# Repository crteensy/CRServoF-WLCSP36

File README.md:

# CRServoF-WLCSP36
CRSF to Servo PWM converter, using an STM32F051 in WLCSP-36

This is a different take on https://github.com/CapnBry/CRServoF, but with major differences - so no fork.

## Purpose and features
Many modern RC receivers have serial output and a number of different serial protocols. A popular one is Crossfire (or CSRF). However, in anything other than multicopters that need a flight controller, these receivers are not very useful because they don't have per-channel PWM output for servos and ESCs.

Theses RC systems also feature telemetry to get data about battery state and many other things on the ground during flight. There are a number of serial protocols for attaching sensors to a receiver for anything that the receiver can't measure itself.

Features:
- STM32F051 in WLCSP-36 *
- CRSF compatible header to attach a receiver to
- 6 Servo PWM outputs
- extra UART header for sensor communication
- Supply for external sensors, either 3V3 or 5V (solder jumper)
- VBat sensing input to an ADC channel, with an on-board divider and filter cap
- LEDs on BEC and 3V3 rails
- SWD header

It is powered by an external BEC (usually the ESC should bring one). There is no regulator on board that will handle anything above 5V. Of course it can run off a 1S LiIon, LiPo or similar battery.

\*) You might ask why I used this package. It's simple: I didn't have any other at hand, and couldn't order any similar STM32 in a more friendly package. It can still be soldered at home, though!

## Layout

The layout is simple and doesn't require special PCB fabrication technology:
- min track width / clearance: 0.1 mm
- standard vias, 0.2 mm drill / 0.5 mm outer diameter, no tenting or similar extras
- 4 layers
- single sided assembly, 0402 or larger passives

In order to route signals that do not come from pins along the perimeter, multiple pins are shorted in order to reach the perimeter. Only one of these pins may drive it at any given time.

MCU Pinout and extra pins used to route the design:

| Function | Pin (GPIO) | Extra Pins (GPIOs) | Comment
|---|---|---|---|
| NRST     | D5 | C6 (PC15) |
| BOOT0    | B4 | B5 (PF0), A6 (PC13) | 10k Pull-down
| PWM 1    | A2 (PA15) |   | TIM2_CH1, 1k series resistor (also boot loader UART Rx)
| PWM 2    | A3 (PB4) |   |  TIM3_CH1, 1k series resistor
| PWM 3    | B3 (PB3) | A4 (PB7) | TIM2_CH2, 1k series resistor
| PWM 4    | F3 (PB0) |   | TIM3_CH3, 1k series resistor
| PWM 5    | D1 (PA9) |   | TIM1_CH2, 1k series resistor
| PWM 6    | F2 (PB1) |   | TIM3_CH4, 1k series resistor
| SWCLK    | B2 (PA14) | A1 (PA12) | (also boot loader Tx, 1k series resistor)
| SWDIO    | B1 (PA13) |   |
| UART1 Tx | C4 (PB6) | C5 (PF1), B6 (PC14)  | 1k series resistor
| UART1 Rx | C1 (PA10) |   |
| UART2 Tx | E4 (PA2) | F4 (PA7) | CRSF header, 1k series resistor
| UART2 Rx | F5 (PA3) |   | CRSF header
| ADC      | F6 (PA0) |   | ADC_IN0, 10k/1k divider and filter cap
| VDD,VDDA | A5, E1, E5 | E6 (PB5) | supply
| VSS, VSSA | F1, D6 |   | GND

The boot loader UART (UART2) on PA14/PA15 can be accessed through a dedicated set of pads on the bottom. One of them (UART2_Tx) is shared with a servo output, but that doesn't hurt during programming.

If the battery voltage (to be measured with the ADC) is accidentally connected to a servo output, this will probably not cause damage because all PWM outputs have a 1k series resistor. Unless it's connected in reverse. That would be bad, even on the VBat header.

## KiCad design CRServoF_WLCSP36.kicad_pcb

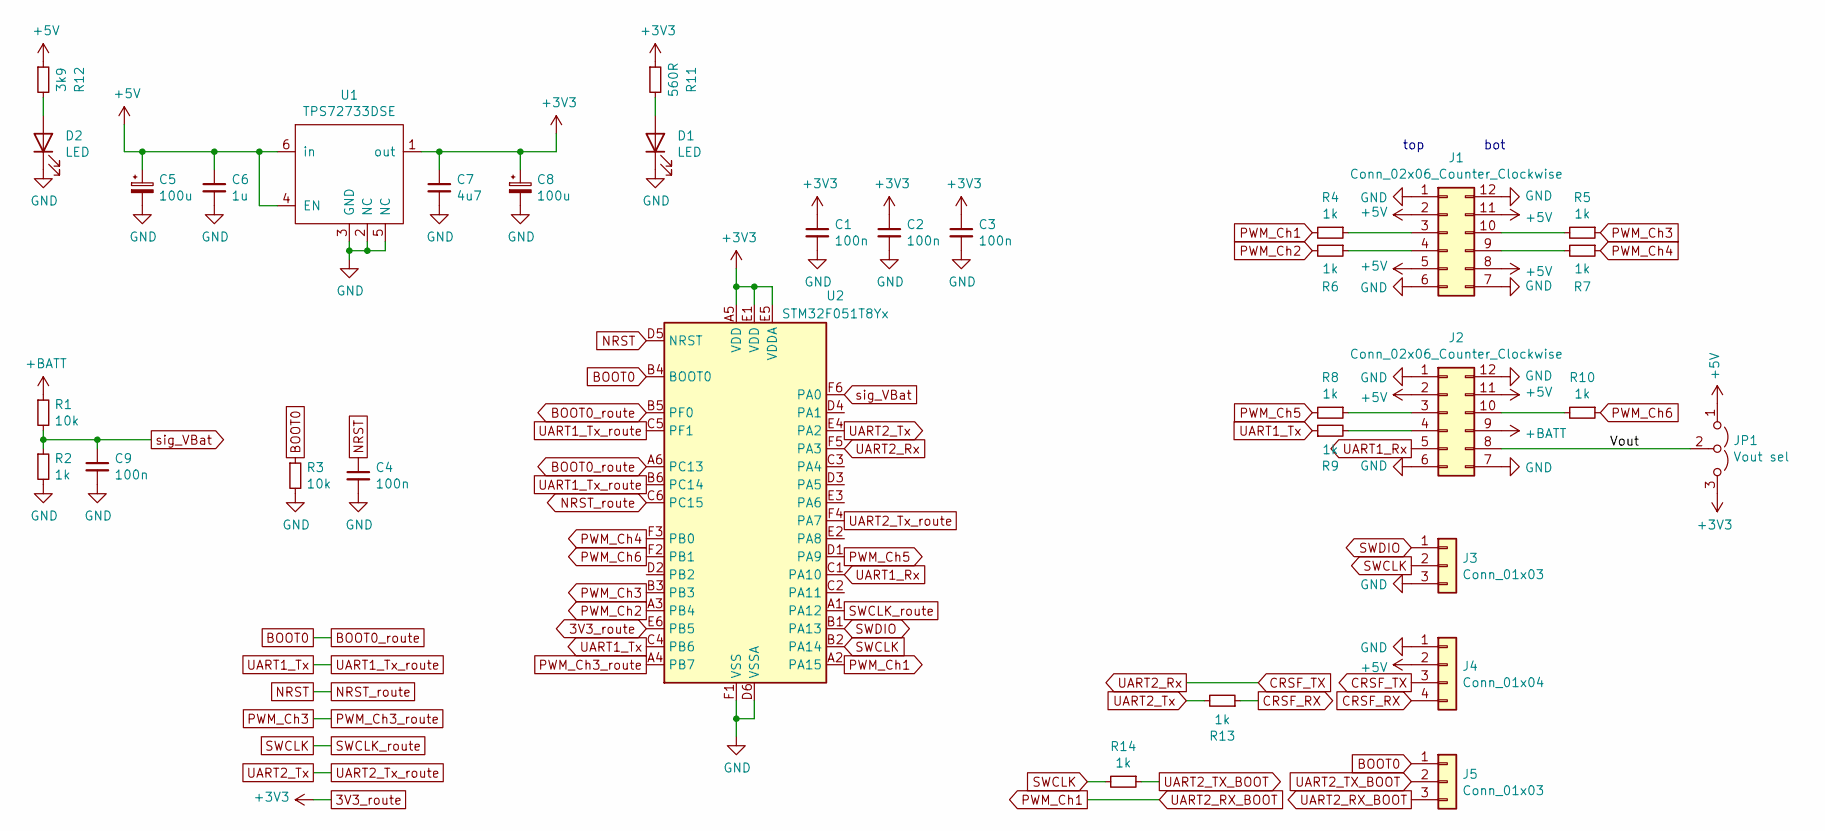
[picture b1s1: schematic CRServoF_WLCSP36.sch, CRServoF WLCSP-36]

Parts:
C1, C2, C3, C4, C9: 100n; C_0402_1005Metric
C5, C8: 100u; CP_EIA-3216-18_Kemet-A
C6: 1u; C_0603_1608Metric
C7: 4u7; C_0603_1608Metric
D1, D2: LED; LED_0402_1005Metric
J1, J2: Conn_02x06_Counter_Clockwise; BoardEdge_Servo_4
J3, J5: Conn_01x03; BoardEdge_Servo_1
J4: Conn_01x04; PinHeader_1x04_P2.54mm_Vertical
JP1: Vout sel; SolderJumper-3_P1.3mm_Open_RoundedPad1.0x1.5mm
R1, R3: 10k; R_0402_1005Metric
R2, R4, R5, R6, R7, R8, R9, R10, R13, R14: 1k; R_0402_1005Metric
R11: 560R; R_0402_1005Metric
R12: 3k9; R_0402_1005Metric
U1: TPS72733DSE; WSON-6_1.5x1.5mm_P0.5mm
U2: STM32F051T8Yx; ST_WLCSP-36_Die440

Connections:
3V3_route: C1.1, C2.1, C3.1, C7.1, C8.1, JP1.3 (B), R11.1, U1.1 (out), U2.A5 (VDD), U2.E1 (VDD), U2.E5 (VDDA), U2.E6 (PB5)
+5V: C5.1, C6.1, J1.2, J1.5, J1.8, J1.11, J2.2, J2.11, J4.2, JP1.1 (A), R12.1, U1.4 (EN), U1.6 (in)
+BATT: J2.9, R1.1
/Vout: J2.8, JP1.2 (C)
BOOT0: J5.1, R3.1, U2.A6 (PC13), U2.B4 (BOOT0), U2.B5 (PF0)
CRSF_RX: J4.4, R13.1
CRSF_TX: J4.3, U2.F5 (PA3)
GND: C1.2, C2.2, C3.2, C4.2, C5.2, C6.2, C7.2, C8.2, C9.2, D1.1 (K), D2.1 (K), J1.1, J1.6, J1.7, J1.12, J2.1, J2.6, J2.7, J2.12, J3.3, J4.1, R2.2, R3.2, U1.2 (NC), U1.3 (GND), U1.5 (NC), U2.D6 (VSSA), U2.F1 (VSS)
NRST: C4.1, U2.C6 (PC15), U2.D5 (NRST)
unnamed: D1.2 (A), R11.2
unnamed: D2.2 (A), R12.2
unnamed: J1.3, R4.1
unnamed: J1.4, R6.1
unnamed: J1.9, R7.2
unnamed: J1.10, R5.2
unnamed: J2.3, R8.1
unnamed: J2.4, R9.2
unnamed: J2.10, R10.2
PWM_Ch1: J5.3, R4.2, U2.A2 (PA15)
PWM_Ch2: R6.2, U2.A3 (PB4)
PWM_Ch3: R5.1, U2.A4 (PB7), U2.B3
PWM_Ch4: R7.1, U2.F3 (PB0)
PWM_Ch5: R8.2, U2.D1 (PA9)
PWM_Ch6: R10.1, U2.F2 (PB1)
SWCLK: J3.2, R14.2, U2.A1 (PA12), U2.B2 (PA14)
SWDIO: J3.1, U2.B1 (PA13)
UART1_Rx: J2.5, U2.C1 (PA10)
UART1_Tx: R9.1, U2.B6 (PC14), U2.C4 (PB6), U2.C5 (PF1)
UART2_TX_BOOT: J5.2, R14.1
UART2_Tx: R13.2, U2.E4 (PA2), U2.F4 (PA7)
sig_VBat: C9.1, R1.2, R2.1, U2.F6 (PA0)

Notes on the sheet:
top
bot

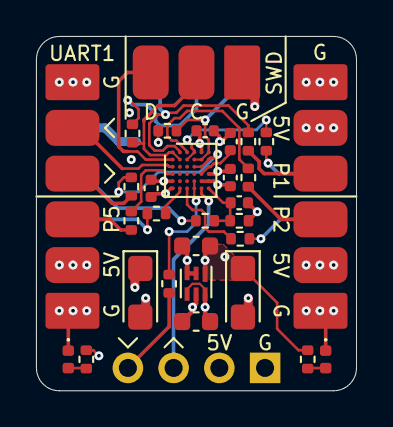
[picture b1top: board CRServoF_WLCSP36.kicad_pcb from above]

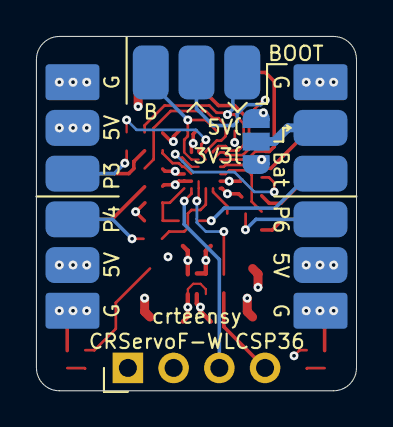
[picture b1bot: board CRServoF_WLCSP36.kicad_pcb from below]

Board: 4 copper layers, 17.8 x 19.7 mm, 33 parts (3 on the bottom side), 31 nets.

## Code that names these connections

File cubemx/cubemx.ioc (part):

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Mcu.Name=STM32F051T8Yx
Mcu.Package=WLCSP36
Mcu.UserName=STM32F051T8Yx
PA0.Mode=IN0
PA0.Signal=ADC_IN0
PA10.Mode=Asynchronous
PA10.Signal=USART1_RX
PA12.GPIOParameters=GPIO_Label
PA12.GPIO_Label=route
PA12.Signal=GPIO_Analog
PA13.Mode=Serial_Wire
PA13.Signal=SYS_SWDIO
PA14.Mode=Serial_Wire
PA14.Signal=SYS_SWCLK
PA15.Signal=S_TIM2_CH1_ETR
PA2.Mode=Asynchronous
PA2.Signal=USART2_TX
PA3.Mode=Asynchronous
PA3.Signal=USART2_RX
PA7.GPIOParameters=GPIO_Label
PA7.GPIO_Label=route
PA7.Signal=GPIO_Analog
PA9.Signal=S_TIM1_CH2
PB0.Signal=S_TIM3_CH3
PB1.Signal=S_TIM3_CH4
PB3.Signal=S_TIM2_CH2
PB4.Signal=S_TIM3_CH1
PB5.GPIOParameters=GPIO_Label
PB5.GPIO_Label=route
PB5.Signal=GPIO_Analog
PB6.Mode=Asynchronous
PB6.Signal=USART1_TX
PB7.GPIOParameters=GPIO_Label
PB7.GPIO_Label=route
PB7.Signal=GPIO_Analog
PC13.GPIOParameters=GPIO_Label
PC13.GPIO_Label=route
PC13.Signal=GPIO_Analog
PC14-OSC32_IN.GPIOParameters=GPIO_Label
PC14-OSC32_IN.GPIO_Label=route
PC14-OSC32_IN.Signal=GPIO_Analog
PC15-OSC32_OUT.GPIOParameters=GPIO_Label
PC15-OSC32_OUT.GPIO_Label=route
PC15-OSC32_OUT.Signal=GPIO_Analog
PF0-OSC_IN.GPIOParameters=GPIO_Label
PF0-OSC_IN.GPIO_Label=route
PF0-OSC_IN.Signal=GPIO_Analog
PF1-OSC_OUT.GPIOParameters=GPIO_Label
PF1-OSC_OUT.GPIO_Label=route
PF1-OSC_OUT.Signal=GPIO_Analog
board=custom

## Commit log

2021-09-30 add design files
2021-09-30 update schematic and silk screen
2021-09-30 Update README.md
    fix PWM output labels
